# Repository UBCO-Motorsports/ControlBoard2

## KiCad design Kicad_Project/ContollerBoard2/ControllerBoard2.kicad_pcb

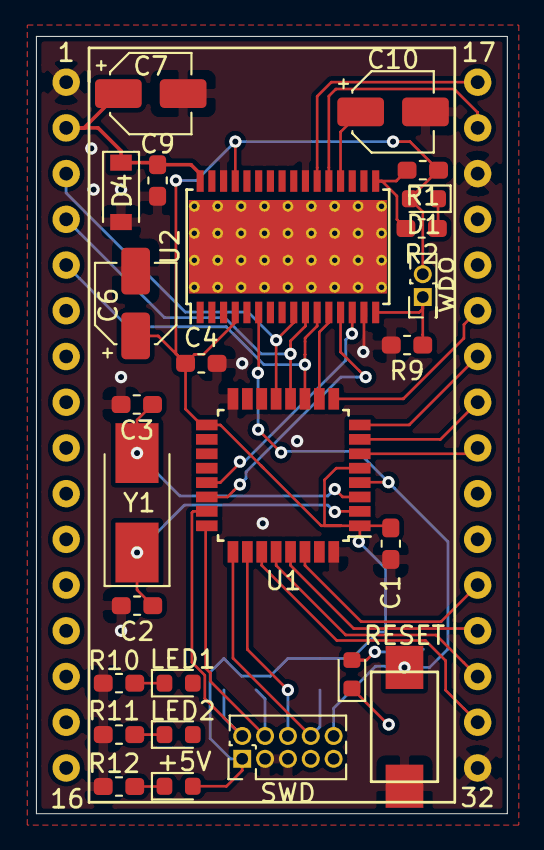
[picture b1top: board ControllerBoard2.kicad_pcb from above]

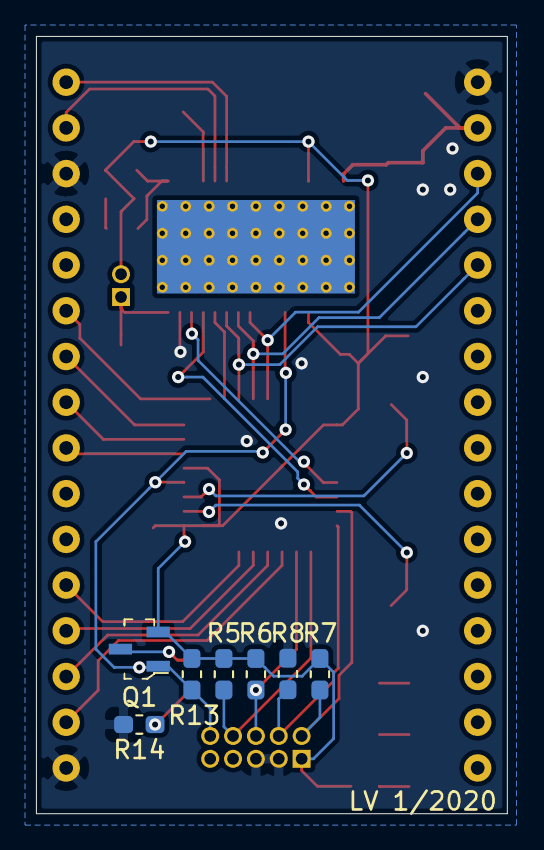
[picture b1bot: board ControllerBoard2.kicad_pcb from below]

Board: 2 copper layers, 26.2 x 43.2 mm, 34 parts (7 on the bottom side), 35 nets.

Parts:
C1, C4, C9: 100n; C_0603_1608Metric_Pad1.05x0.95mm_HandSolder
C2, C3: 18p; C_0603_1608Metric_Pad1.05x0.95mm_HandSolder
C6, C7, C10: 10u; CP_Elec_4x5.4
D1, D6: LEDR; LED_0603_1608Metric
D2, D3, D5: LEDG; LED_0603_1608Metric
D4: 30v; D_SOD-123
J1: Main Header; Breadboard_Center_32pin
J2: SWD; PinHeader_2x05_P1.27mm_Vertical
J3: WD_Disable; PinHeader_2x01_P1.27mm_Vertical
Q1: BSS84; SOT-23-3
R1, R5, R6, R7, R8, R13: 10k; R_0603_1608Metric_Pad1.05x0.95mm_HandSolder
R2, R10, R11, R12, R14: 220; R_0603_1608Metric_Pad1.05x0.95mm_HandSolder
R9: 1.3k; R_0603_1608Metric_Pad1.05x0.95mm_HandSolder
S1: RESET; PTS636 SK25F SMTR LFS
U1: STM32F303K8Tx; LQFP-32_7x7mm_P0.8mm
U2: UJA1075A-3.3; HTSSOP-32-1EP_6.1x11mm_P0.65mm_EP5.2x11mm_Mask4.11x4.36mm_T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
Y1: 8Mhz; Crystal_SMD_Abracon_ABM3-2Pin_5.0x3.2mm_HandSoldering

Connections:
+3V3: C1.2, C4.1, C6.1, D1.2, D5.2, J2.1, J3.2, Q1.2, R1.1, R5.1, R6.1, R7.1, R13.1, U1.1, U1.5, U1.17, U2.4, U2.29
+12V: C7.1, C9.2, D4.1, J1.2, U2.32
CANH: J1.18, U2.21
CANL: J1.17, U2.22
CAN_RX: U1.21, U2.14
CAN_TX: U1.22, U2.13
GND: C1.1, C2.2, C3.2, C4.2, C6.2, C7.2, C9.1, C10.2, D4.2, J1.1, J1.19, J1.32, J2.3, J2.5, R8.2, R9.2, R10.1, R11.1, R12.1, R14.2, S1.2, U1.16, U1.32, U2.15, U2.23, U2.30
LIMP: R1.2, R2.2, U2.17
MISO: J1.4, U1.12, U2.10
MOSI: J1.3, U1.13, U2.9
unnamed: C10.1, U2.20
unnamed: D1.1, R2.1
unnamed: D2.1, R10.2
unnamed: D3.1, R11.2
unnamed: D5.1, R12.2
unnamed: D6.1, R14.1
unnamed: D6.2, Q1.3
OSC_IN: C2.1, U1.2, Y1.1
OSC_OUT: C3.1, U1.3, Y1.2
PA0: J1.25, U1.6
PA1: J1.24, U1.7
PA2: J1.23, U1.8
PA3: J1.22, U1.9
PB4: J1.31, U1.27
PB5: J1.30, U1.28
PB6: J1.29, U1.29
PB7: J1.28, U1.30
RESET: J2.10, Q1.1, R13.2, S1.1, U1.4, U2.6
SCK: J1.5, U1.11, U2.11
SCSN: U1.10, U2.12
SWDCLK: J2.4, R8.1, U1.24
SWDIO: J2.2, R7.2, U1.23
SWO: J2.6, R6.2, U1.26
TDI: J2.8, R5.2, U1.25
WD_OFF: J3.1, R9.1, U2.16

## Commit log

2020-09-21 Added kicad project
2020-09-21 Added .gitignore
2020-09-24 Brought PCBNew document over from v1
2020-09-30 First draft of controlboard2
2020-10-01 Created base STM32Cube project
2020-10-01 Generated CLion project dependencies
2020-10-01 Modified CMAKE config for Clion
    CMAKE was modified in order for FREERTOS to compile succesfully. FPU had to be enabled.
